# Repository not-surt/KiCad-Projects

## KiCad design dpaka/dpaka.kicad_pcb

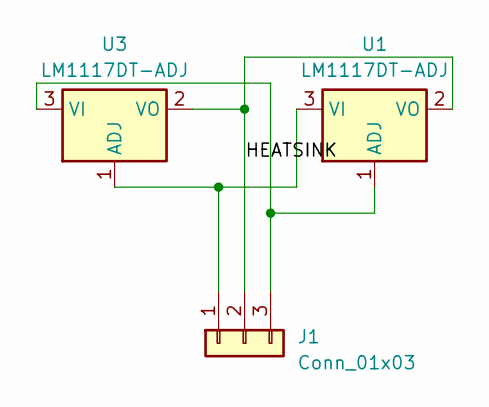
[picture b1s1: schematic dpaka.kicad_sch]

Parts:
J1: Conn_01x03; PinHeader_1x03_P2.54mm_Vertical
U1: LM1117DT-ADJ; TO-263-3_TabPin2
U3: LM1117DT-ADJ; TO-252-3_TabPin2

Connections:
/HEATSINK: J1.2, U1.2 (VO), U3.2 (VO)
unnamed: J1.1, U1.3 (VI), U3.1 (ADJ)
unnamed: J1.3, U1.1 (ADJ), U3.3 (VI)

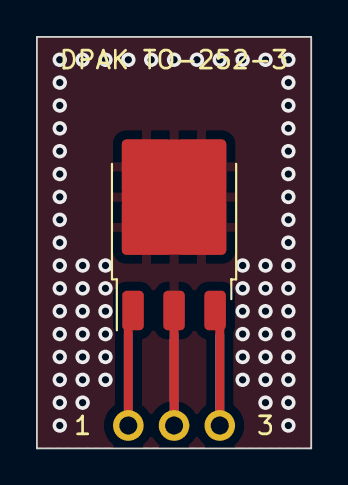
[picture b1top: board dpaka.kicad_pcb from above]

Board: 2 copper layers, 15.2 x 22.9 mm, 3 parts (1 on the bottom side), 3 nets.

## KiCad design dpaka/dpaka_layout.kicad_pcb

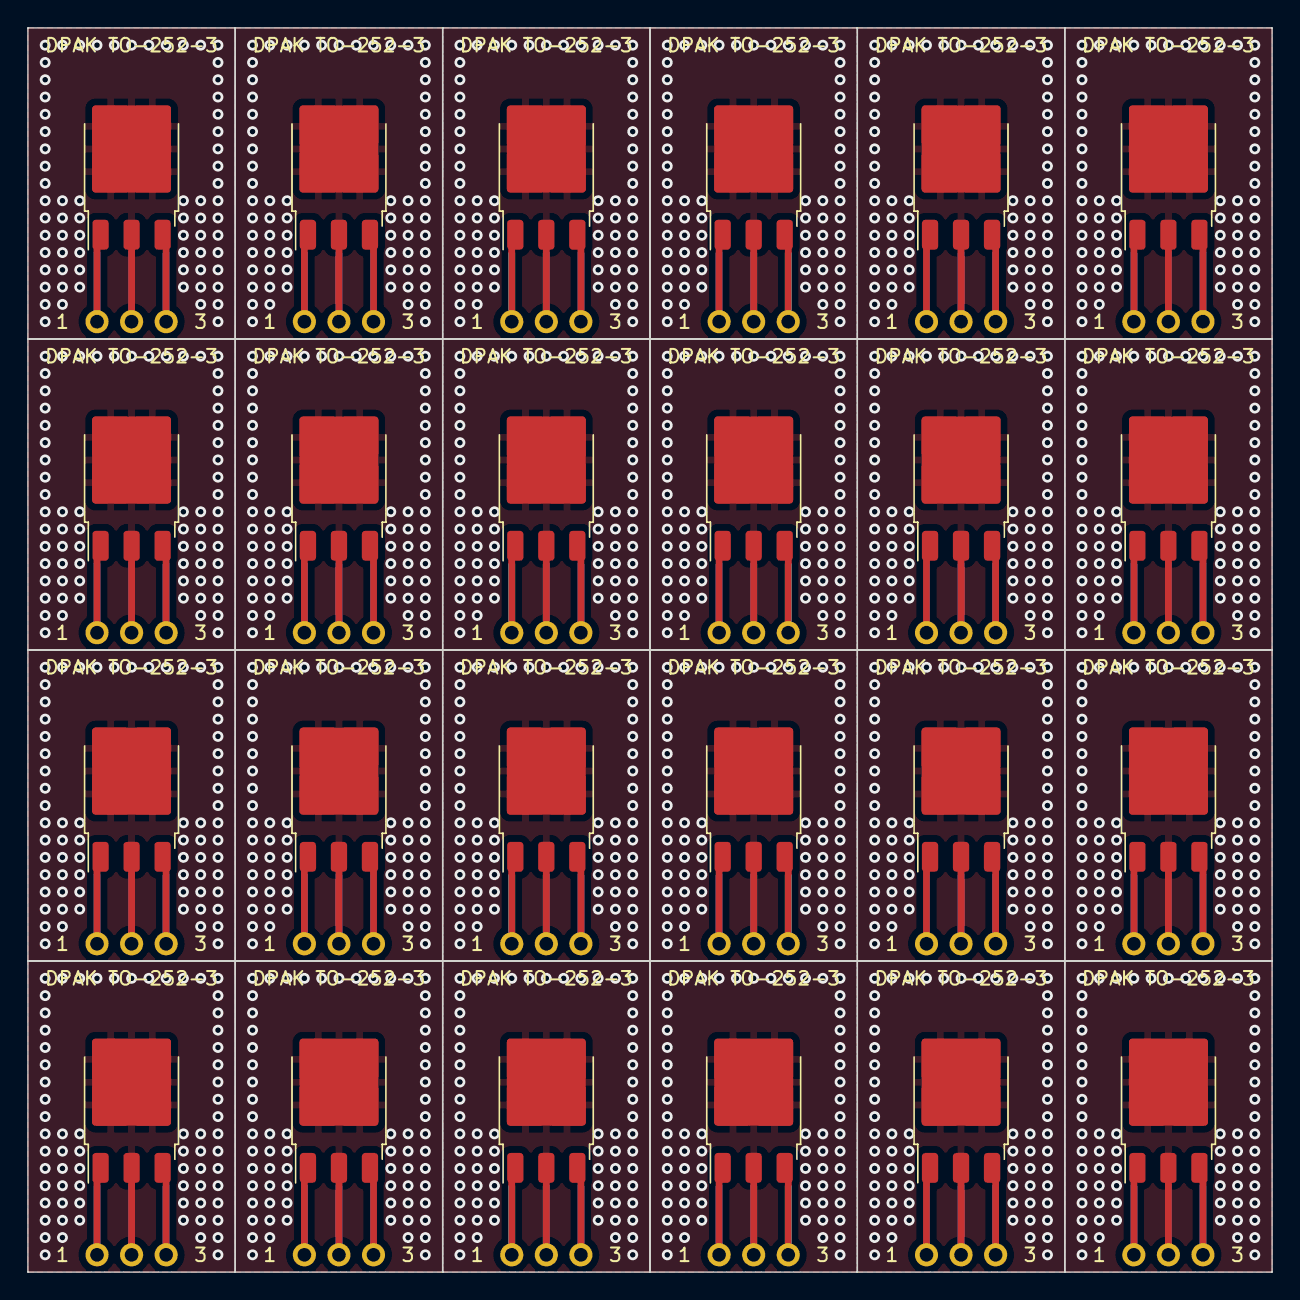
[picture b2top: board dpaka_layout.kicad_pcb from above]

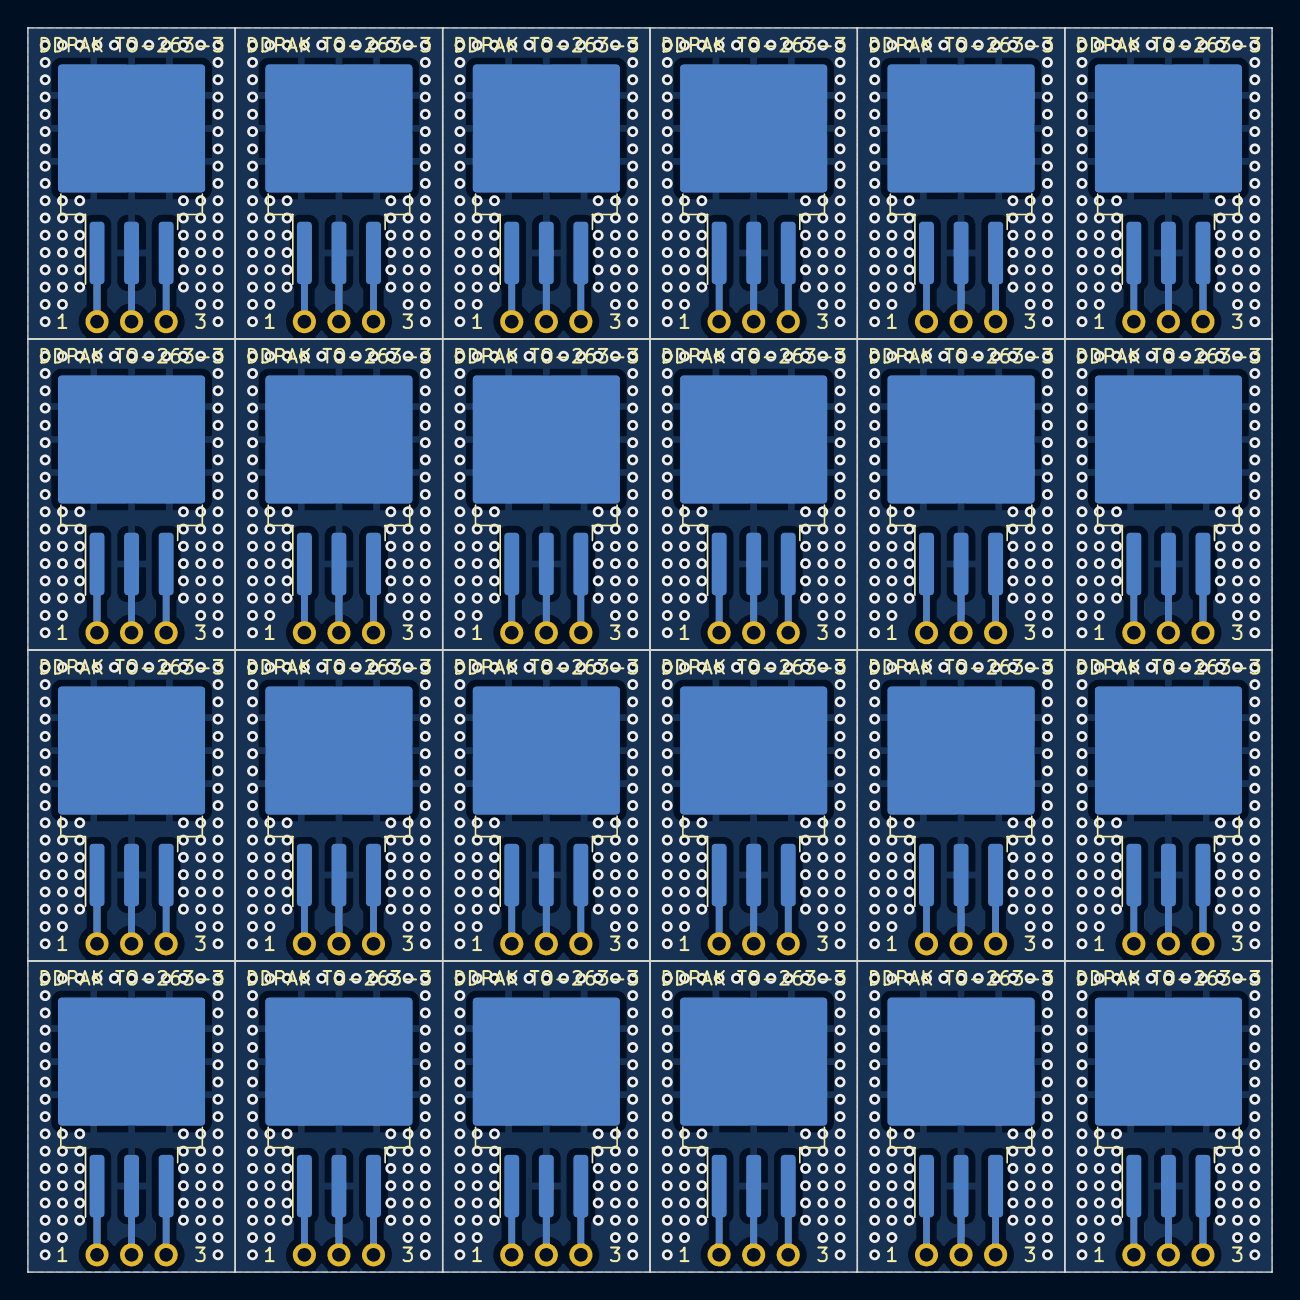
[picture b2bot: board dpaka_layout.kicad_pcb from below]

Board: 2 copper layers, 91.4 x 91.4 mm, 72 parts (24 on the bottom side), 3 nets.

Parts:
J1, J2, J3, J4, J5, J6, J7, J8, J9, J10, J11, J12, J13, J14, J15, J16, J17, J18, J19, J20, J21, J22, J23, J24: Conn_01x03; PinHeader_1x03_P2.54mm_Vertical
U1, U2, U5, U7, U9, U11, U13, U15, U17, U19, U21, U23, U25, U27, U29, U31, U33, U35, U37, U39, U41, U43, U45, U47: LM1117DT-ADJ; TO-263-3_TabPin2
U3, U4, U6, U8, U10, U12, U14, U16, U18, U20, U22, U24, U26, U28, U30, U32, U34, U36, U38, U40, U42, U44, U46, U48: LM1117DT-ADJ; TO-252-3_TabPin2

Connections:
/HEATSINK: J1.2, J2.2, J3.2, J4.2, J5.2, J6.2, J7.2, J8.2, J9.2, J10.2, J11.2, J12.2, J13.2, J14.2, J15.2, J16.2, J17.2, J18.2, J19.2, J20.2, J21.2, J22.2, J23.2, J24.2, U1.2 (VO), U2.2 (VO), U3.2 (VO), U4.2 (VO), U5.2 (VO), U6.2 (VO), U7.2 (VO), U8.2 (VO), U9.2 (VO), U10.2 (VO), U11.2 (VO), U12.2 (VO), U13.2 (VO), U14.2 (VO), U15.2 (VO), U16.2 (VO), U17.2 (VO), U18.2 (VO), U19.2 (VO), U20.2 (VO), U21.2 (VO), U22.2 (VO), U23.2 (VO), U24.2 (VO), U25.2 (VO), U26.2 (VO), U27.2 (VO), U28.2 (VO), U29.2 (VO), U30.2 (VO), U31.2 (VO), U32.2 (VO), U33.2 (VO), U34.2 (VO), U35.2 (VO), U36.2 (VO), U37.2 (VO), U38.2 (VO), U39.2 (VO), U40.2 (VO), U41.2 (VO), U42.2 (VO), U43.2 (VO), U44.2 (VO), U45.2 (VO), U46.2 (VO), U47.2 (VO), U48.2 (VO)
unnamed: J1.1, J2.1, J3.1, J4.1, J5.1, J6.1, J7.1, J8.1, J9.1, J10.1, J11.1, J12.1, J13.1, J14.1, J15.1, J16.1, J17.1, J18.1, J19.1, J20.1, J21.1, J22.1, J23.1, J24.1, U1.3 (VI), U2.3 (VI), U3.1 (ADJ), U4.1 (ADJ), U5.3 (VI), U6.1 (ADJ), U7.3 (VI), U8.1 (ADJ), U9.3 (VI), U10.1 (ADJ), U11.3 (VI), U12.1 (ADJ), U13.3 (VI), U14.1 (ADJ), U15.3 (VI), U16.1 (ADJ), U17.3 (VI), U18.1 (ADJ), U19.3 (VI), U20.1 (ADJ), U21.3 (VI), U22.1 (ADJ), U23.3 (VI), U24.1 (ADJ), U25.3 (VI), U26.1 (ADJ), U27.3 (VI), U28.1 (ADJ), U29.3 (VI), U30.1 (ADJ), U31.3 (VI), U32.1 (ADJ), U33.3 (VI), U34.1 (ADJ), U35.3 (VI), U36.1 (ADJ), U37.3 (VI), U38.1 (ADJ), U39.3 (VI), U40.1 (ADJ), U41.3 (VI), U42.1 (ADJ), U43.3 (VI), U44.1 (ADJ), U45.3 (VI), U46.1 (ADJ), U47.3 (VI), U48.1 (ADJ)
unnamed: J1.3, J2.3, J3.3, J4.3, J5.3, J6.3, J7.3, J8.3, J9.3, J10.3, J11.3, J12.3, J13.3, J14.3, J15.3, J16.3, J17.3, J18.3, J19.3, J20.3, J21.3, J22.3, J23.3, J24.3, U1.1 (ADJ), U2.1 (ADJ), U3.3 (VI), U4.3 (VI), U5.1 (ADJ), U6.3 (VI), U7.1 (ADJ), U8.3 (VI), U9.1 (ADJ), U10.3 (VI), U11.1 (ADJ), U12.3 (VI), U13.1 (ADJ), U14.3 (VI), U15.1 (ADJ), U16.3 (VI), U17.1 (ADJ), U18.3 (VI), U19.1 (ADJ), U20.3 (VI), U21.1 (ADJ), U22.3 (VI), U23.1 (ADJ), U24.3 (VI), U25.1 (ADJ), U26.3 (VI), U27.1 (ADJ), U28.3 (VI), U29.1 (ADJ), U30.3 (VI), U31.1 (ADJ), U32.3 (VI), U33.1 (ADJ), U34.3 (VI), U35.1 (ADJ), U36.3 (VI), U37.1 (ADJ), U38.3 (VI), U39.1 (ADJ), U40.3 (VI), U41.1 (ADJ), U42.3 (VI), U43.1 (ADJ), U44.3 (VI), U45.1 (ADJ), U46.3 (VI), U47.1 (ADJ), U48.3 (VI)

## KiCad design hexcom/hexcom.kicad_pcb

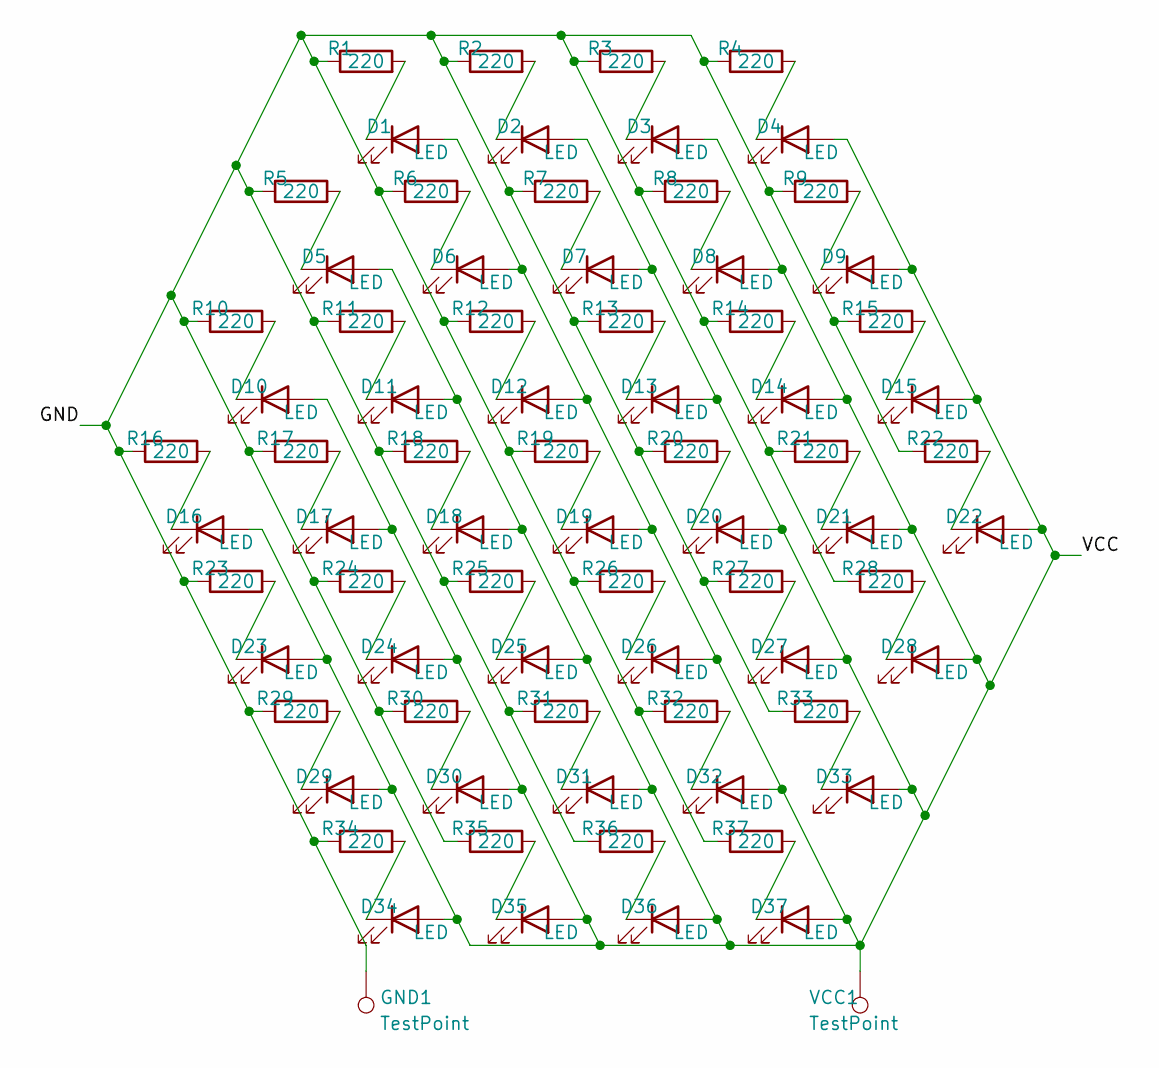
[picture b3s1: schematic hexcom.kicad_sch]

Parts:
D1, D2, D3, D4, D5, D6, D7, D8, D9, D10, D11, D12, D13, D14, D15, D16, D17, D18, D19, D20, D21, D22, D23, D24, D25, D26, D27, D28, D29, D30, D31, D32, D33, D34, D35, D36, D37: LED; LED_D5.0mm
GND1: TestPoint; TestPoint_Pad_4.0x4.0mm
R1, R2, R3, R4, R5, R6, R7, R8, R9, R10, R11, R12, R13, R14, R15, R16, R17, R18, R19, R20, R21, R22, R23, R24, R25, R26, R27, R28, R29, R30, R31, R32, R33, R34, R35, R36, R37: 220; R_Axial_DIN0207_L6.3mm_D2.5mm_P7.62mm_Horizontal
VCC1: TestPoint; TestPoint_Pad_D4.0mm

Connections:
/GND: GND1.1, R1.1, R2.1, R3.1, R4.1, R5.1, R6.1, R7.1, R8.1, R9.1, R10.1, R11.1, R12.1, R13.1, R14.1, R15.1, R16.1, R17.1, R18.1, R19.1, R20.1, R21.1, R22.1, R23.1, R24.1, R25.1, R26.1, R27.1, R28.1, R29.1, R30.1, R31.1, R32.1, R33.1, R34.1, R35.1, R36.1, R37.1
/VCC: D1.2 (A), D2.2 (A), D3.2 (A), D4.2 (A), D5.2 (A), D6.2 (A), D7.2 (A), D8.2 (A), D9.2 (A), D10.2 (A), D11.2 (A), D12.2 (A), D13.2 (A), D14.2 (A), D15.2 (A), D16.2 (A), D17.2 (A), D18.2 (A), D19.2 (A), D20.2 (A), D21.2 (A), D22.2 (A), D23.2 (A), D24.2 (A), D25.2 (A), D26.2 (A), D27.2 (A), D28.2 (A), D29.2 (A), D30.2 (A), D31.2 (A), D32.2 (A), D33.2 (A), D34.2 (A), D35.2 (A), D36.2 (A), D37.2 (A), VCC1.1
unnamed: D1.1 (K), R1.2
unnamed: D2.1 (K), R2.2
unnamed: D3.1 (K), R3.2
unnamed: D4.1 (K), R4.2
unnamed: D5.1 (K), R5.2
unnamed: D6.1 (K), R6.2
unnamed: D7.1 (K), R7.2
unnamed: D8.1 (K), R8.2
unnamed: D9.1 (K), R9.2
unnamed: D10.1 (K), R10.2
unnamed: D11.1 (K), R11.2
unnamed: D12.1 (K), R12.2
unnamed: D13.1 (K), R13.2
unnamed: D14.1 (K), R14.2
unnamed: D15.1 (K), R15.2
unnamed: D16.1 (K), R16.2
unnamed: D17.1 (K), R17.2
unnamed: D18.1 (K), R18.2
unnamed: D19.1 (K), R19.2
unnamed: D20.1 (K), R20.2
unnamed: D21.1 (K), R21.2
unnamed: D22.1 (K), R22.2
unnamed: D23.1 (K), R23.2
unnamed: D24.1 (K), R24.2
unnamed: D25.1 (K), R25.2
unnamed: D26.1 (K), R26.2
unnamed: D27.1 (K), R27.2
unnamed: D28.1 (K), R28.2
unnamed: D29.1 (K), R29.2
unnamed: D30.1 (K), R30.2
unnamed: D31.1 (K), R31.2
unnamed: D32.1 (K), R32.2
unnamed: D33.1 (K), R33.2
unnamed: D34.1 (K), R34.2
unnamed: D35.1 (K), R35.2
unnamed: D36.1 (K), R36.2
unnamed: D37.1 (K), R37.2

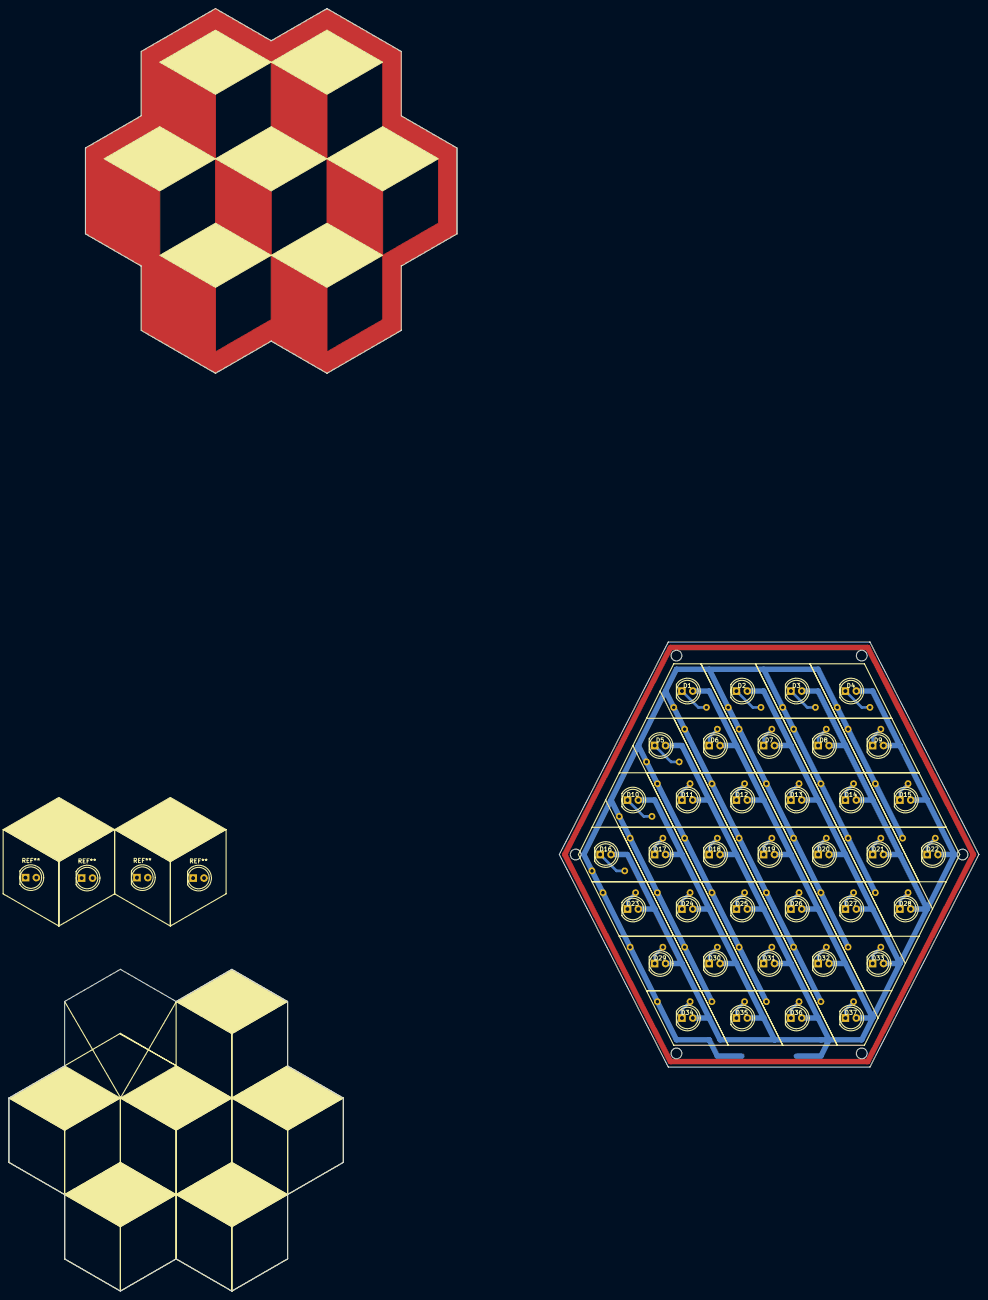
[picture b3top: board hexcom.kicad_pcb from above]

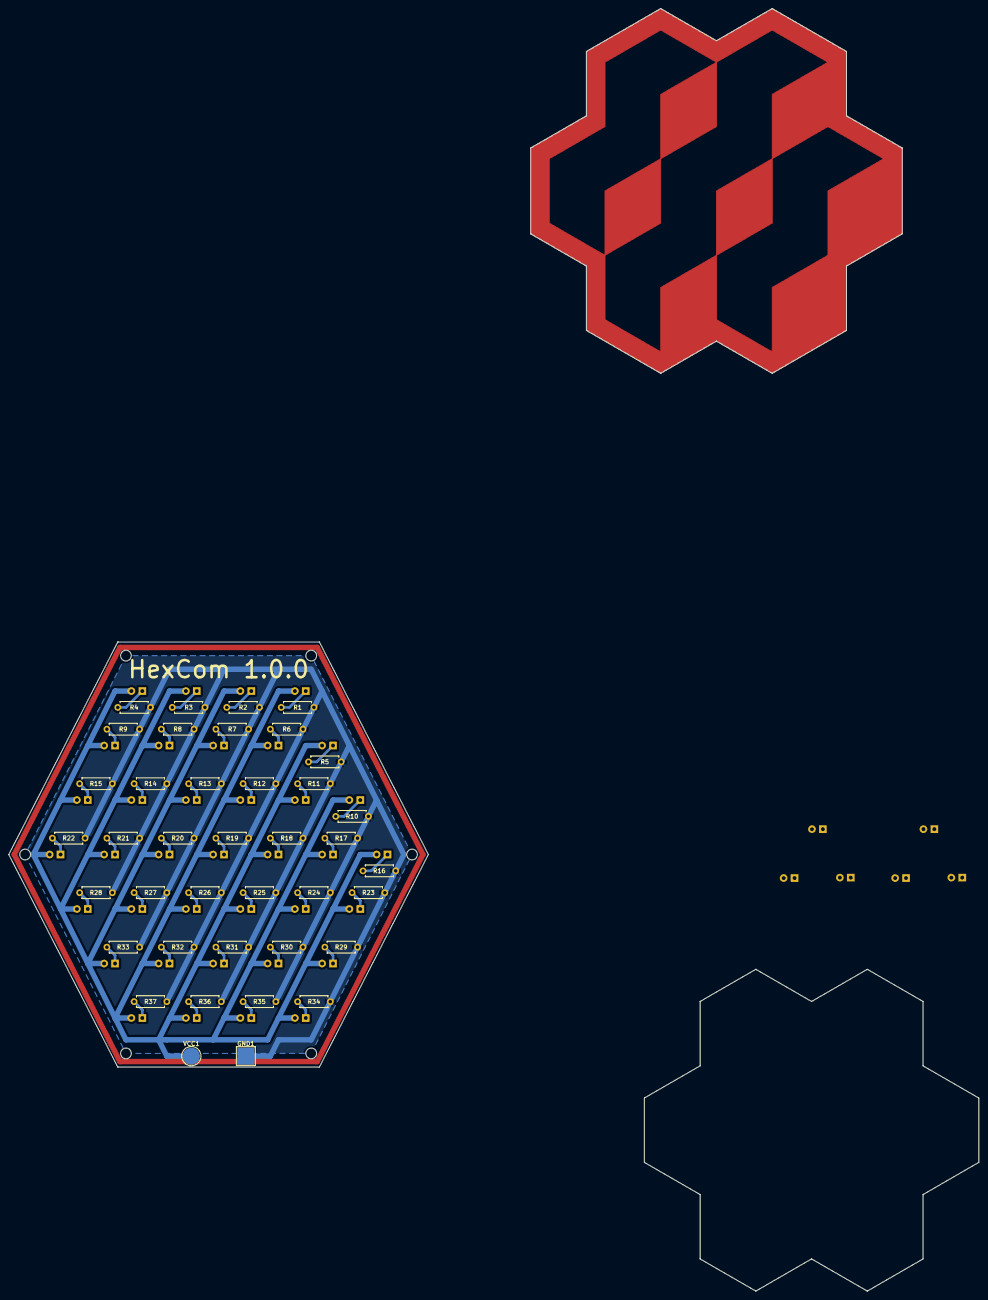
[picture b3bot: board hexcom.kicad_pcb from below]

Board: 2 copper layers, 97.8 x 99.1 mm, 76 parts (39 on the bottom side), 39 nets.

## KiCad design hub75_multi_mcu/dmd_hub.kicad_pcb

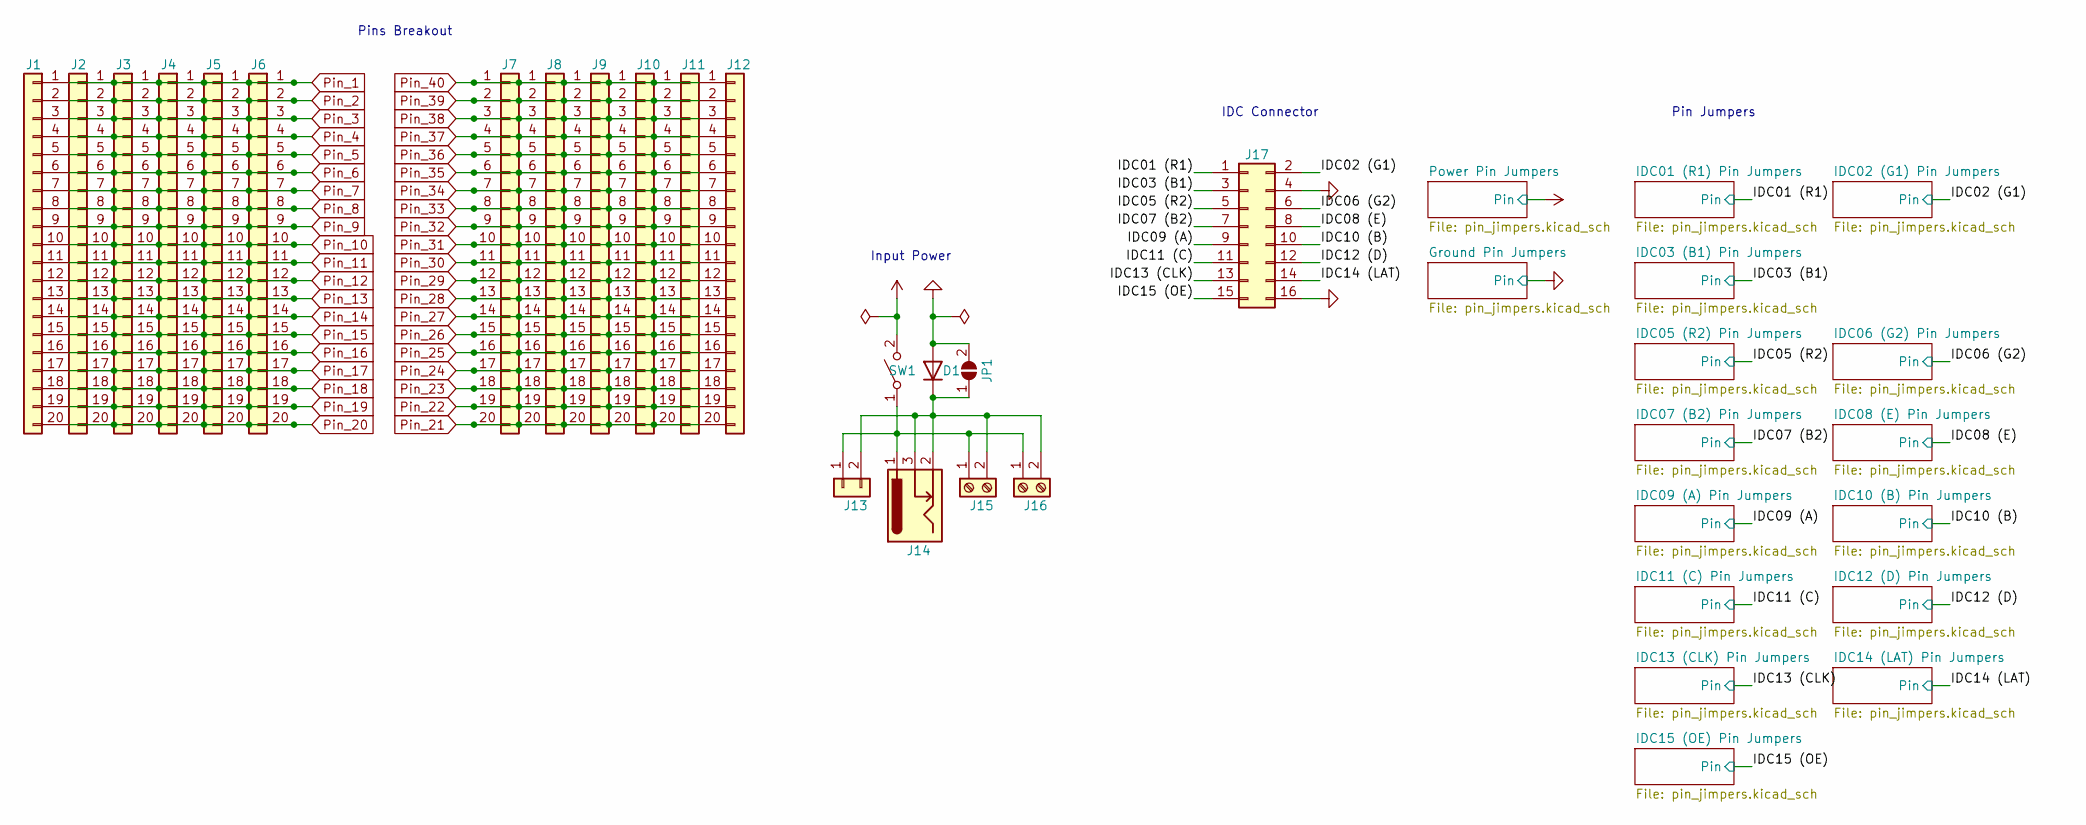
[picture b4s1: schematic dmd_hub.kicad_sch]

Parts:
D1: D; D_SMA
J1, J2, J3, J4, J5, J6, J7, J8, J9, J10, J11, J12: Conn_01x20; PinHeader_1x20_P2.54mm_Vertical_No_Silk
J13: Conn_01x02; PinHeader_1x02_P2.54mm_Vertical
J14: Barrel_Jack; BarrelJack_Horizontal
J15: Screw_Terminal_01x02; TerminalBlock_bornier-2_P5.08mm
J16: Screw_Terminal_01x02; Barrier_Block
J17: Conn_02x08_Odd_Even; IDC-Header_2x08_P2.54mm_Vertical
JP1: SolderJumper_2_Open; SolderJumper-2_P1.3mm_Open_RoundedPad1.0x1.5mm
SW1: SW_SPST; SW_E-Switch_EG1271_SPDT

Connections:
/IDC01 (R1): J17.1; also elsewhere on the board
/IDC02 (G1): J17.2; also elsewhere on the board
/IDC03 (B1): J17.3; also elsewhere on the board
/IDC05 (R2): J17.5; also elsewhere on the board
/IDC06 (G2): J17.6; also elsewhere on the board
/IDC07 (B2): J17.7; also elsewhere on the board
/IDC08 (E): J17.8; also elsewhere on the board
/IDC09 (A): J17.9; also elsewhere on the board
/IDC10 (B): J17.10; also elsewhere on the board
/IDC11 (C): J17.11; also elsewhere on the board
/IDC12 (D): J17.12; also elsewhere on the board
/IDC13 (CLK): J17.13; also elsewhere on the board
/IDC14 (LAT): J17.14; also elsewhere on the board
/IDC15 (OE): J17.15; also elsewhere on the board
GND: D1.2 (A), J17.4, J17.16, JP1.2 (B); also elsewhere on the board
unnamed: D1.1 (K), J13.2, J14.2, J14.3, J15.2, J16.2, JP1.1 (A)
unnamed: J13.1, J14.1, J15.1, J16.1, SW1.1 (A)
Pin_1: J1.1, J2.1, J3.1, J4.1, J5.1, J6.1; also elsewhere on the board
Pin_2: J1.2, J2.2, J3.2, J4.2, J5.2, J6.2; also elsewhere on the board
Pin_3: J1.3, J2.3, J3.3, J4.3, J5.3, J6.3; also elsewhere on the board
Pin_4: J1.4, J2.4, J3.4, J4.4, J5.4, J6.4; also elsewhere on the board
Pin_5: J1.5, J2.5, J3.5, J4.5, J5.5, J6.5; also elsewhere on the board
Pin_6: J1.6, J2.6, J3.6, J4.6, J5.6, J6.6; also elsewhere on the board
Pin_7: J1.7, J2.7, J3.7, J4.7, J5.7, J6.7; also elsewhere on the board
Pin_8: J1.8, J2.8, J3.8, J4.8, J5.8, J6.8; also elsewhere on the board
Pin_9: J1.9, J2.9, J3.9, J4.9, J5.9, J6.9; also elsewhere on the board
Pin_10: J1.10, J2.10, J3.10, J4.10, J5.10, J6.10; also elsewhere on the board
Pin_11: J1.11, J2.11, J3.11, J4.11, J5.11, J6.11; also elsewhere on the board
Pin_12: J1.12, J2.12, J3.12, J4.12, J5.12, J6.12; also elsewhere on the board
Pin_13: J1.13, J2.13, J3.13, J4.13, J5.13, J6.13; also elsewhere on the board
Pin_14: J1.14, J2.14, J3.14, J4.14, J5.14, J6.14; also elsewhere on the board
Pin_15: J1.15, J2.15, J3.15, J4.15, J5.15, J6.15; also elsewhere on the board
Pin_16: J1.16, J2.16, J3.16, J4.16, J5.16, J6.16; also elsewhere on the board
Pin_17: J1.17, J2.17, J3.17, J4.17, J5.17, J6.17; also elsewhere on the board
Pin_18: J1.18, J2.18, J3.18, J4.18, J5.18, J6.18; also elsewhere on the board
Pin_19: J1.19, J2.19, J3.19, J4.19, J5.19, J6.19; also elsewhere on the board
Pin_20: J1.20, J2.20, J3.20, J4.20, J5.20, J6.20; also elsewhere on the board
Pin_21: J7.20, J8.20, J9.20, J10.20, J11.20, J12.20; also elsewhere on the board
Pin_22: J7.19, J8.19, J9.19, J10.19, J11.19, J12.19; also elsewhere on the board
Pin_23: J7.18, J8.18, J9.18, J10.18, J11.18, J12.18; also elsewhere on the board
Pin_24: J7.17, J8.17, J9.17, J10.17, J11.17, J12.17; also elsewhere on the board
Pin_25: J7.16, J8.16, J9.16, J10.16, J11.16, J12.16; also elsewhere on the board
Pin_26: J7.15, J8.15, J9.15, J10.15, J11.15, J12.15; also elsewhere on the board
Pin_27: J7.14, J8.14, J9.14, J10.14, J11.14, J12.14; also elsewhere on the board
Pin_28: J7.13, J8.13, J9.13, J10.13, J11.13, J12.13; also elsewhere on the board
Pin_29: J7.12, J8.12, J9.12, J10.12, J11.12, J12.12; also elsewhere on the board
Pin_30: J7.11, J8.11, J9.11, J10.11, J11.11, J12.11; also elsewhere on the board
Pin_31: J7.10, J8.10, J9.10, J10.10, J11.10, J12.10; also elsewhere on the board
Pin_32: J7.9, J8.9, J9.9, J10.9, J11.9, J12.9; also elsewhere on the board
Pin_33: J7.8, J8.8, J9.8, J10.8, J11.8, J12.8; also elsewhere on the board
Pin_34: J7.7, J8.7, J9.7, J10.7, J11.7, J12.7; also elsewhere on the board
Pin_35: J7.6, J8.6, J9.6, J10.6, J11.6, J12.6; also elsewhere on the board
Pin_36: J7.5, J8.5, J9.5, J10.5, J11.5, J12.5; also elsewhere on the board
Pin_37: J7.4, J8.4, J9.4, J10.4, J11.4, J12.4; also elsewhere on the board
Pin_38: J7.3, J8.3, J9.3, J10.3, J11.3, J12.3; also elsewhere on the board
Pin_39: J7.2, J8.2, J9.2, J10.2, J11.2, J12.2; also elsewhere on the board
Pin_40: J7.1, J8.1, J9.1, J10.1, J11.1, J12.1; also elsewhere on the board
VCC: SW1.2 (B); also elsewhere on the board

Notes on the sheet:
Pins Breakout
IDC Connector
Input Power
Pin Jumpers
